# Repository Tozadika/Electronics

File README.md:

# PS-DC-3V3-2A

Thank you to read this readme file
It's an simple electronic project.

-----------------------------------------------------
Intro

Simple board for electronic enthousiastic who are looking for compact, and powerfull module to power supply 3.3Vdc logic circuit.
All design is based on the Maxim Integrated MAX17643 synchronous step-down DC-DC Converter with internal compensation.

Basic technical data :

Input voltage : 4.5V to 60 Vdc
Output voltage : 3.3 Vdc
Maximum output current : 2A

-----------------------------------------------------
Specific component for this project

All specifics components are include on Components folder.
To configure kicad to recognize symbol and footprint on start, add a variable : ${PROJ_REPO} : path to your root project folder.

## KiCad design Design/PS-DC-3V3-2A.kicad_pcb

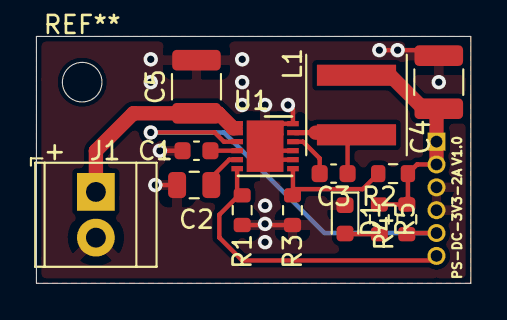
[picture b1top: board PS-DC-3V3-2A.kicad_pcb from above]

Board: 2 copper layers, 24.1 x 13.7 mm, 15 parts (1 on the bottom side), 11 nets.

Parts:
C1: 5.6n; C_0603_1608Metric
C2: 4.7u; C_0805_2012Metric
C3: 0.1u; C_0603_1608Metric
C4: 47u; C_1210_3225Metric
C5: 2.2u; C_1210_3225Metric
D1: LED_Green; LED_0603_1608Metric
J1: Conn_01x02; TerminalBlock_TE_282834-2_1x02_P2.54mm_Horizontal
J2: Conn_01x06; PinHeader_1x06_P1.27mm_Vertical
L1: 6.8u; L_Coilcraft_XAL5050-682
R1: 40.2k; R_0603_1608Metric
R2: 52.3k; R_0603_1608Metric
R3: 19.6k; R_0603_1608Metric
R4: 10k; R_0603_1608Metric
R5: 65R; R_0603_1608Metric
U1: MAX17643; DFN-12-1EP_3x3mm_P0.5mm_EP2.05x2.86mm

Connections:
GND: C1.2, C2.2, C4.2, C5.1, D1.1, J1.2, J2.3, J2.4, R1.2, R3.2, U1.8, U1.9, U1.12, U1.13
unnamed: C1.1, U1.4
unnamed: C2.1, U1.5
unnamed: C3.1, U1.10
unnamed: C3.2, L1.1, U1.11
unnamed: D1.2, R5.2
unnamed: R2.2, R3.1, U1.7
SYNC: J2.6, R1.1, U1.6
Vin: C5.2, J1.1, U1.1, U1.2
Vout: C4.1, J2.1, J2.2, L1.2, R2.1, R4.2, R5.1
\Reset: J2.5, R4.1, U1.3

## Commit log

2021-04-12 Init repository
2021-04-12 Init schematic folio
2021-04-12 Add Coilcraft inductor associated datasheet
2021-04-12 Add Coilcraft 5050-682 inductor, have to add 3d file!
2021-04-12 add .gitignore to the repo
2021-04-12 Create scheamtic
2021-04-12 Create pcb, draft done, have to clean pcb layers, improve routing, add 3dfiles to libraries
2021-04-12 Change library path with PROJ_REPO variable
2021-04-13 Add 3D files, from CoilCraft and TE
2021-04-13 Attach 3d file to CoilCraft
2021-04-13 Add Sync and reset components, re-arange
2021-04-13 Change output conenctor references, add reset and sync pull-down
2021-04-13 Change Con_1x04 => Con_1x06
2021-04-13 Add BOM, Drill files, Gerber files, step (have to be adjust), position files
2021-04-24 Suppress pull-down resistaor on nReset signal, replaced by 10k pull-up
2021-04-24 Change resistor reference
2021-04-24 change connector J2 reference
2021-04-24 Drill file updated
2021-04-24 Pull up resistor update
2021-04-24 Update position file
2021-04-24 M2 mounting hole added
2021-04-25 Add green led on output pin
2021-04-25 Add led to the board
2021-04-25 Add led lib to the design
2021-04-25 Add Q_PMOS, and a Zener diode on input pin
2021-04-25 Add Zener resistor, res=verse Zener
2021-04-27 Add ibom module and ibom file to the repo
